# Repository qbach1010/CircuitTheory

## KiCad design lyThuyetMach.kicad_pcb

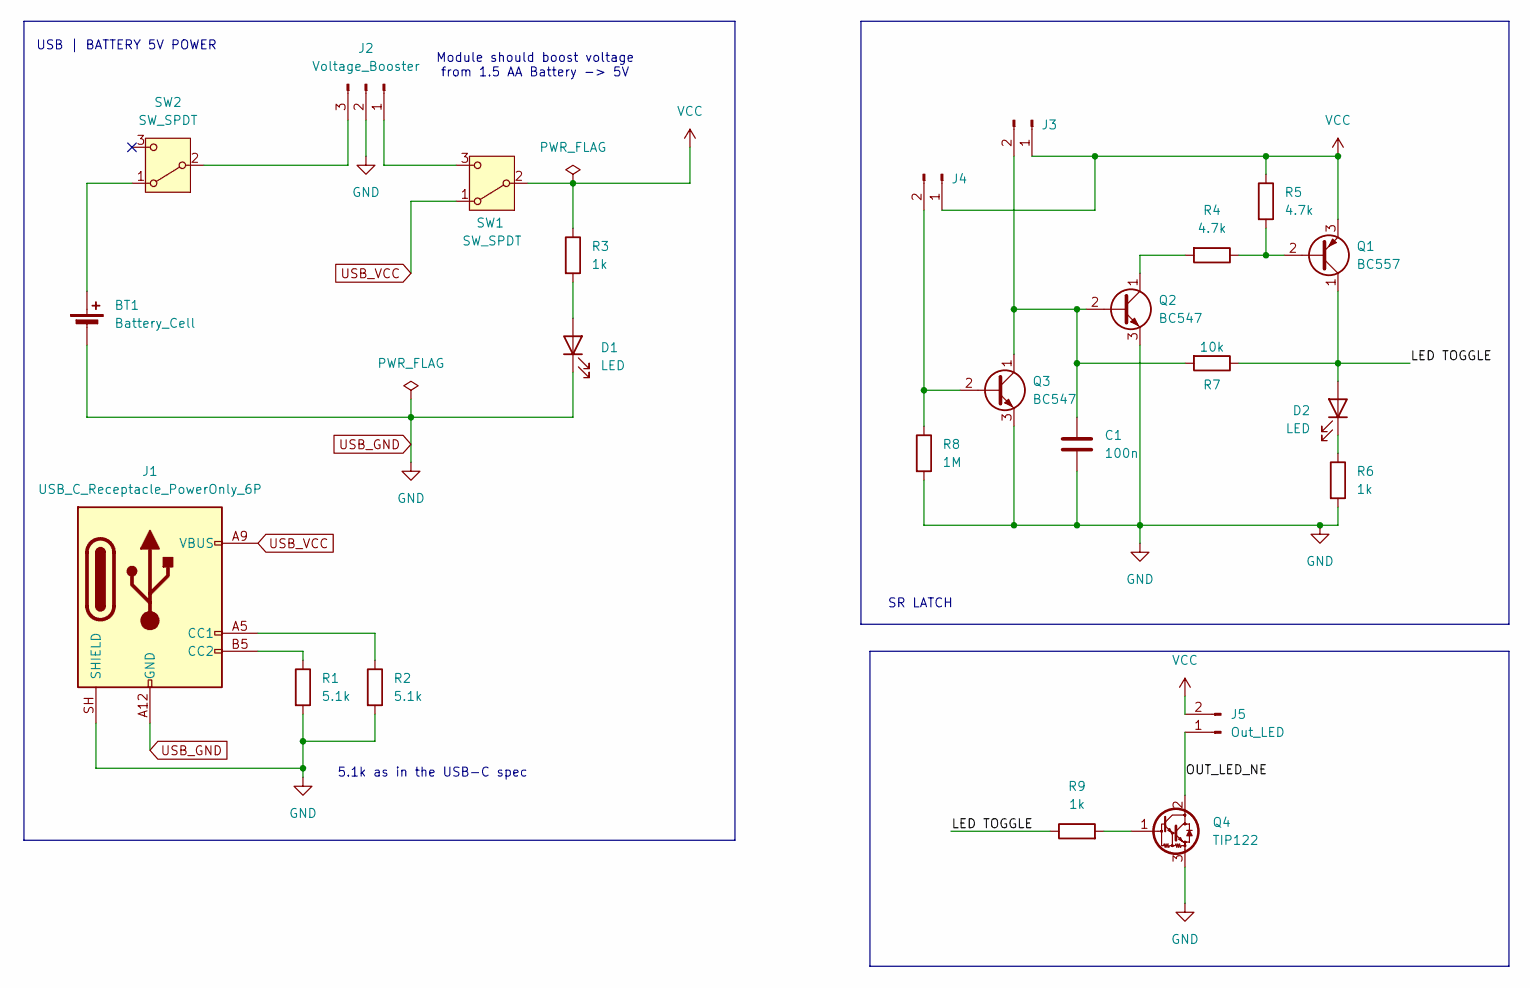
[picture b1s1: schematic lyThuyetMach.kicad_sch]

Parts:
BT1: Battery_Cell; BatteryHolder_Keystone_2460_1xAA
C1: 100n; C_Disc_D5.0mm_W2.5mm_P5.00mm
D1: LED; LED_D5.0mm_FlatTop
D2: LED; LED_D5.0mm
J1: USB_C_Receptacle_PowerOnly_6P; USB_C_Receptacle_HRO_TYPE-C-31-M-17
J2: Voltage_Booster; PinHeader_1x03_P2.54mm_Vertical
J3, J4: Conn_01x02_Pin; R_0815_2038Metric_Pad1.20x4.05mm_HandSolder
J5: Out_LED; PinHeader_1x02_P2.54mm_Vertical
Q1: BC557; TO-92_Inline
Q2, Q3: BC547; TO-92_Inline
Q4: TIP122; TO-220-3_Vertical
R1, R2: 5.1k; R_Axial_DIN0207_L6.3mm_D2.5mm_P10.16mm_Horizontal
R3, R6, R9: 1k; R_Axial_DIN0207_L6.3mm_D2.5mm_P10.16mm_Horizontal
R4, R5: 4.7k; R_Axial_DIN0207_L6.3mm_D2.5mm_P10.16mm_Horizontal
R7: 10k; R_Axial_DIN0207_L6.3mm_D2.5mm_P10.16mm_Horizontal
R8: 1M; R_Axial_DIN0207_L6.3mm_D2.5mm_P10.16mm_Horizontal
SW1, SW2: SW_SPDT; PinHeader_1x03_P2.54mm_Vertical

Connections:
/LED TOGGLE: D2.2 (A), Q1.1 (C), R7.1, R9.1
/OUT_LED_NE: J5.1, Q4.2 (C)
unnamed: BT1.1 (+), SW2.1 (A)
unnamed: D1.2 (A), R3.2
unnamed: D2.1 (K), R6.1
unnamed: J1.A5 (CC1), R2.1
unnamed: J1.B5 (CC2), R1.1
unnamed: J2.1, SW1.3 (C)
unnamed: J2.3, SW2.2 (B)
unnamed: C1.1, J3.2, Q2.2 (B), Q3.1 (C), R7.2
unnamed: J4.2, Q3.2 (B), R8.1
unnamed: Q1.2 (B), R4.1, R5.2
unnamed: Q2.1 (C), R4.2
unnamed: Q4.1 (B), R9.2
USB_GND: BT1.2 (-), C1.2, D1.1 (K), J1.A12 (GND), J1.B12 (GND), J1.SH (SHIELD), J2.2, Q2.3 (E), Q3.3 (E), Q4.3 (E), R1.2, R2.2, R6.2, R8.2
USB_VCC: J1.A9 (VBUS), J1.B9 (VBUS), SW1.1 (A)
VCC: J3.1, J4.1, J5.2, Q1.3 (E), R3.1, R5.1, SW1.2 (B)

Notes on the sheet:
SR LATCH
USB | BATTERY 5V POWER
5.1k as in the USB-C spec
Module should boost voltage from 1.5 AA Battery -> 5V

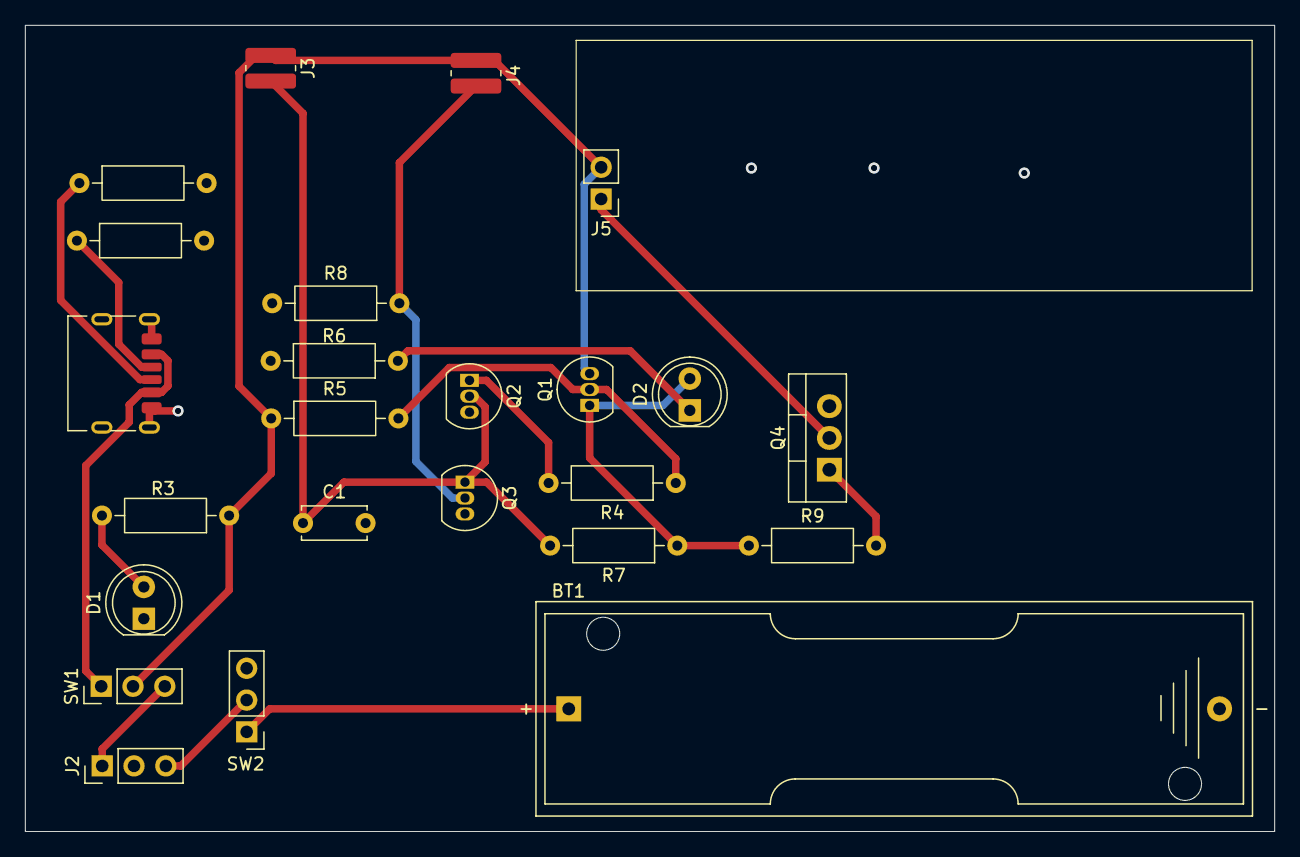
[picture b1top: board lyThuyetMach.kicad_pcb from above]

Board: 2 copper layers, 99.8 x 64.4 mm, 24 parts (0 on the bottom side), 17 nets.
